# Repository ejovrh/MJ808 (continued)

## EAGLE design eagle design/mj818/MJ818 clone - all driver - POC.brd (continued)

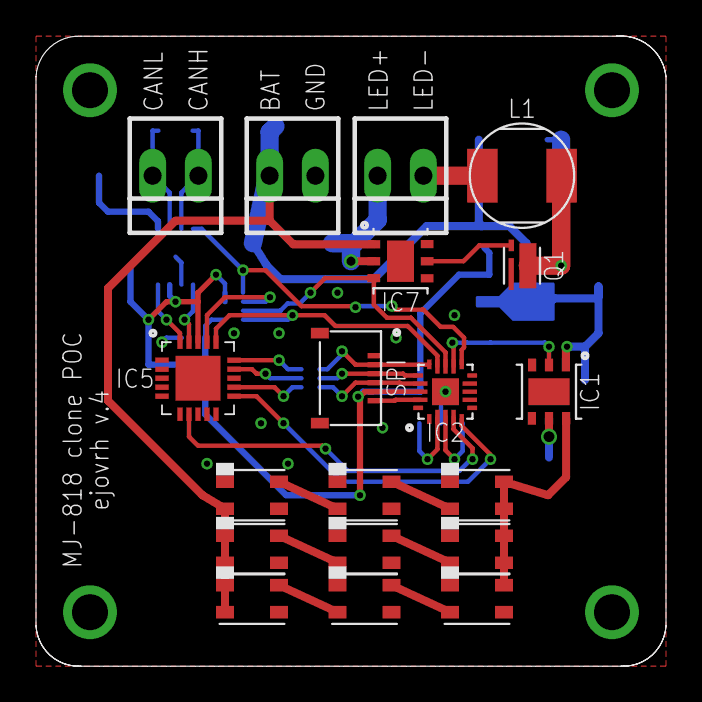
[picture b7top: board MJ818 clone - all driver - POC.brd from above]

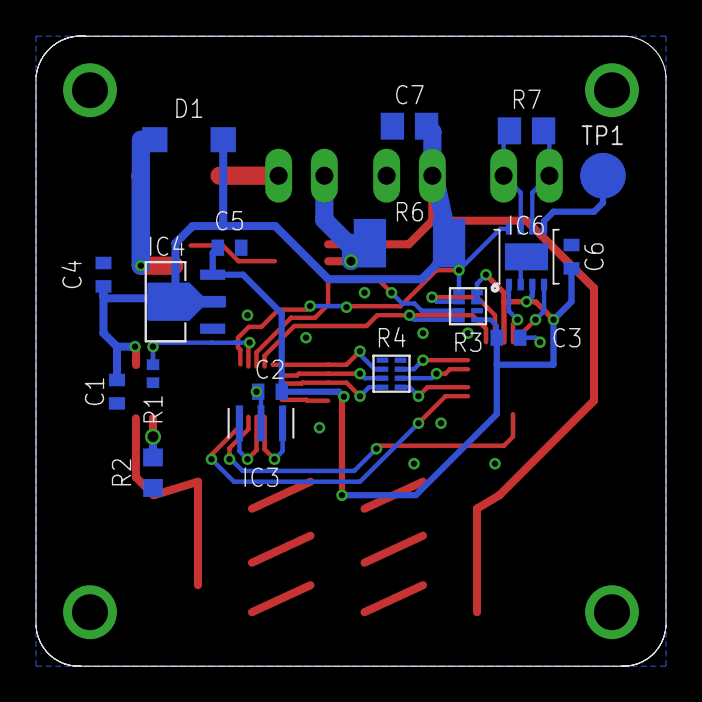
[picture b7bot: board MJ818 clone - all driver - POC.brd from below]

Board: 2 copper layers, 35.0 x 35.0 mm, 37 parts (18 on the bottom side), 36 nets.

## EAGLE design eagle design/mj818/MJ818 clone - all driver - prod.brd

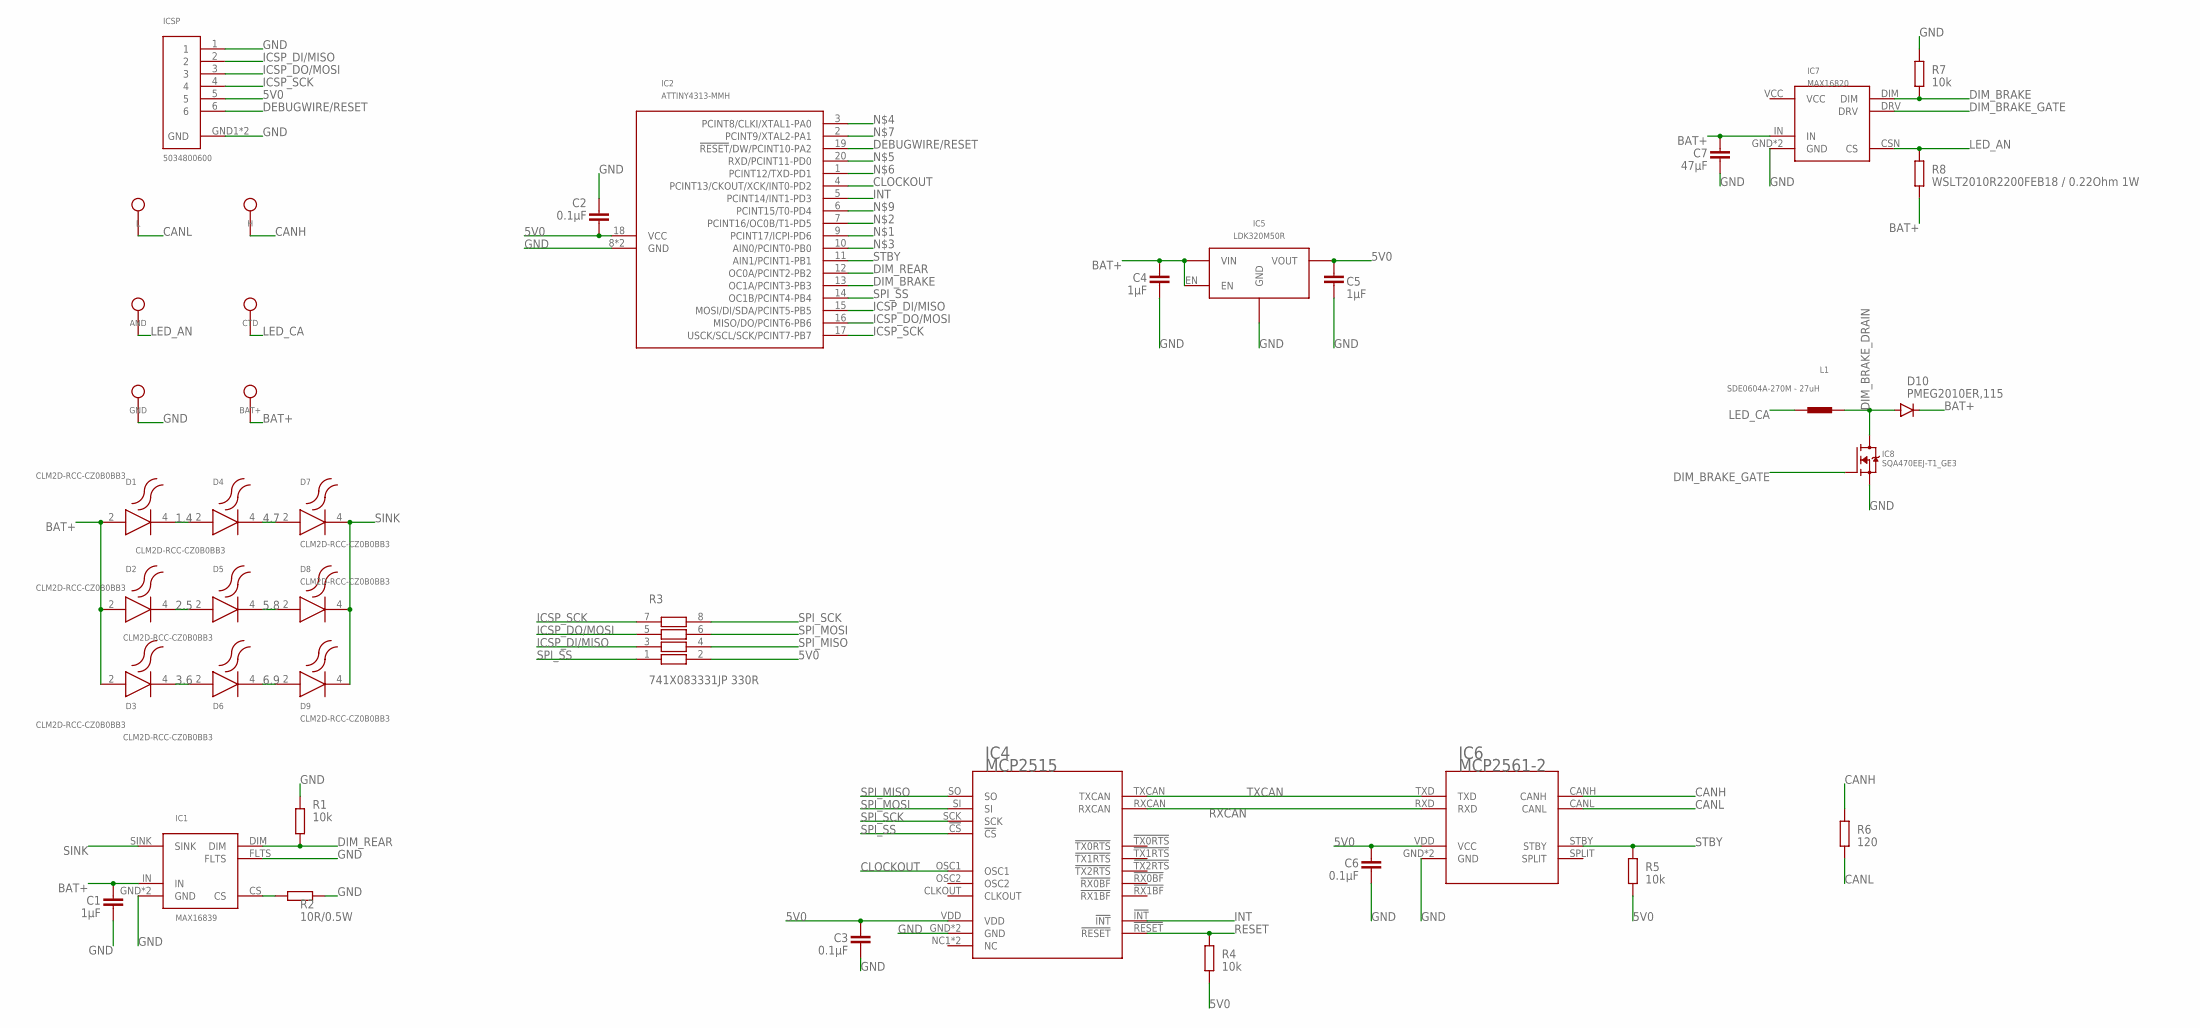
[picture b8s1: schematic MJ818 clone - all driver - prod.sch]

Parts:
AND: LED anode; SMT-1.2MM
BAT+: bat+; TH-1.2MM
C1, C4, C5: 1μF; C0402
C2, C3, C6: 0.1μF; C0402
C7: 47μF; C1206
CTD: LED cathode; SMT-1.2MM
D1, D2, D3, D4, D5, D6, D7, D8, D9: CLM2D-RCC-CZ0B0BB3; SMD
D10: PMEG2010ER,115; SOD123
GND: gnd; TH-1.2MM
H: LED anode; TH-1.2MM
IC1: MAX16839; TDFN-6-EP
IC2: ATTINY4313-MMH; VQFN-20
IC4: MCP2515; QFN20
IC5: LDK320M50R; SOT-23-5L
IC6: MCP2561-2; DFN10
IC7: MAX16820; TDFN-6-EP
IC8: SQA470EEJ-T1_GE3; SC-70-6
ICSP: 5034800600; SMT
L: LED anode; TH-1.2MM
L1: SDE0604A-270M - 27uH; SMT
R1, R4, R5, R7: 10k; R0402
R2: 10R/0.5W; R0603
R3: 741X083331JP 330R; 0402
R6: 120; R0805
R8: WSLT2010R2200FEB18 / 0.22Ohm 1W; R2010

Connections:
1.4: D1.4 (C), D4.2 (A)
2.5: D2.4 (C), D5.2 (A)
3.6: D3.4 (C), D6.2 (A)
4.7: D4.4 (C), D7.2 (A)
5.8: D5.4 (C), D8.2 (A)
5V0: C2.1, C3.1, C5.2, C6.1, IC2.18 (VCC), IC4.VDD, IC5.OUT (VOUT), IC6.VDD (VCC), ICSP.5, R3.2, R4.1, R5.1
6.9: D6.4 (C), D9.2 (A)
BAT+: BAT+.TP$1, C1.2, C4.1, C7.1, D1.2 (A), D2.2 (A), D3.2 (A), D10.C, IC1.IN, IC5.EN, IC5.IN (VIN), IC7.IN, R8.2
CANH: H.TP$1, IC6.CANH, R6.2
CANL: IC6.CANL, L.TP$1, R6.1
CLOCKOUT: IC2.4 (PCINT13/CKOUT/XCK/INT0-PD2), IC4.OSC1
CS: IC1.CS, R2.1
DEBUGWIRE/RESET: IC2.19 (!RESET!/DW/PCINT10-PA2), ICSP.6
DIM_BRAKE: IC2.13 (OC1A/PCINT3-PB3), IC7.DIM, R7.1
DIM_BRAKE_DRAIN: D10.A, IC8.1D (D), IC8.2D (D), IC8.5D (D), IC8.6D (D), IC8.D, L1.P$2
DIM_BRAKE_GATE: IC7.DRV, IC8.3G (G)
DIM_REAR: IC1.DIM, IC2.12 (OC0A/PCINT2-PB2), R1.1
GND: C1.1, C2.2, C3.2, C4.2, C5.1, C6.2, C7.2, GND.TP$1, IC1.FLTS, IC1.GND, IC1.GND1 (GND), IC2.8 (GND), IC2.GND, IC4.GND, IC4.GND6 (GND), IC5.GND, IC6.GND, IC6.VSS (GND), IC7.GND, IC7.GND1 (GND), IC8.4S (S), IC8.S, ICSP.1, ICSP.GND1 (GND), ICSP.GND2 (GND), R1.2, R2.2, R7.2
ICSP_DI/MISO: IC2.15 (MOSI/DI/SDA/PCINT5-PB5), ICSP.2, R3.3
ICSP_DO/MOSI: IC2.16 (MISO/DO/PCINT6-PB6), ICSP.3, R3.5
ICSP_SCK: IC2.17 (USCK/SCL/SCK/PCINT7-PB7), ICSP.4, R3.7
INT: IC2.5 (PCINT14/INT1-PD3), IC4.!INT!
LED_AN: AND.P$1, IC7.CSN (CS), R8.1
LED_CA: CTD.P$1, L1.P$1
RESET: IC4.!RESET!, R4.2
RXCAN: IC4.RXCAN, IC6.RXD
SINK: D7.4 (C), D8.4 (C), D9.4 (C), IC1.SINK
SPI_MISO: IC4.SO, R3.4
SPI_MOSI: IC4.SI, R3.6
SPI_SCK: IC4.SCK, R3.8
SPI_SS: IC2.14 (OC1B/PCINT4-PB4), IC4.!CS!, R3.1
STBY: IC2.11 (AIN1/PCINT1-PB1), IC6.STBY, R5.2
TXCAN: IC4.TXCAN, IC6.TXD
VCC: IC7.VCC

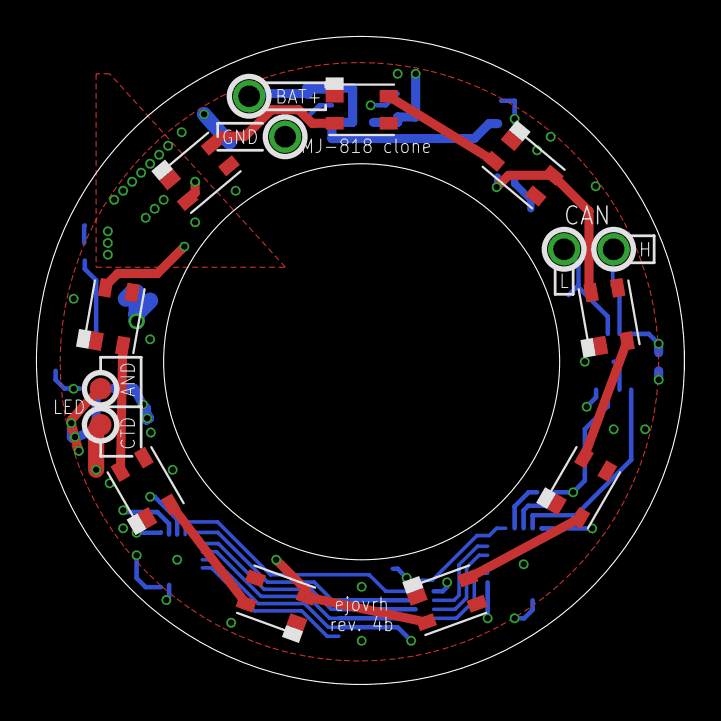
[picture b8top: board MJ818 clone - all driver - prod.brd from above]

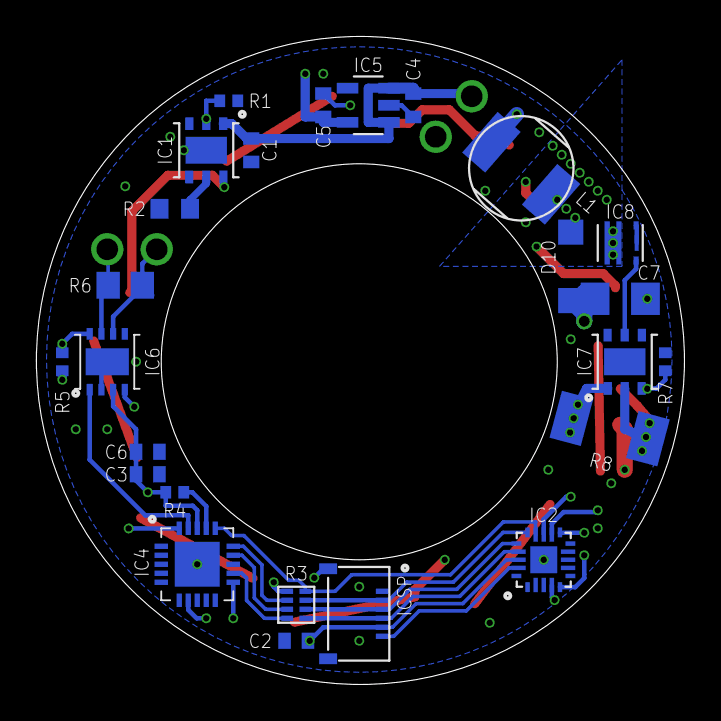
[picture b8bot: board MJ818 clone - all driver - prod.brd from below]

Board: 4 copper layers, 36.0 x 36.0 mm, 40 parts (25 on the bottom side), 33 nets.
